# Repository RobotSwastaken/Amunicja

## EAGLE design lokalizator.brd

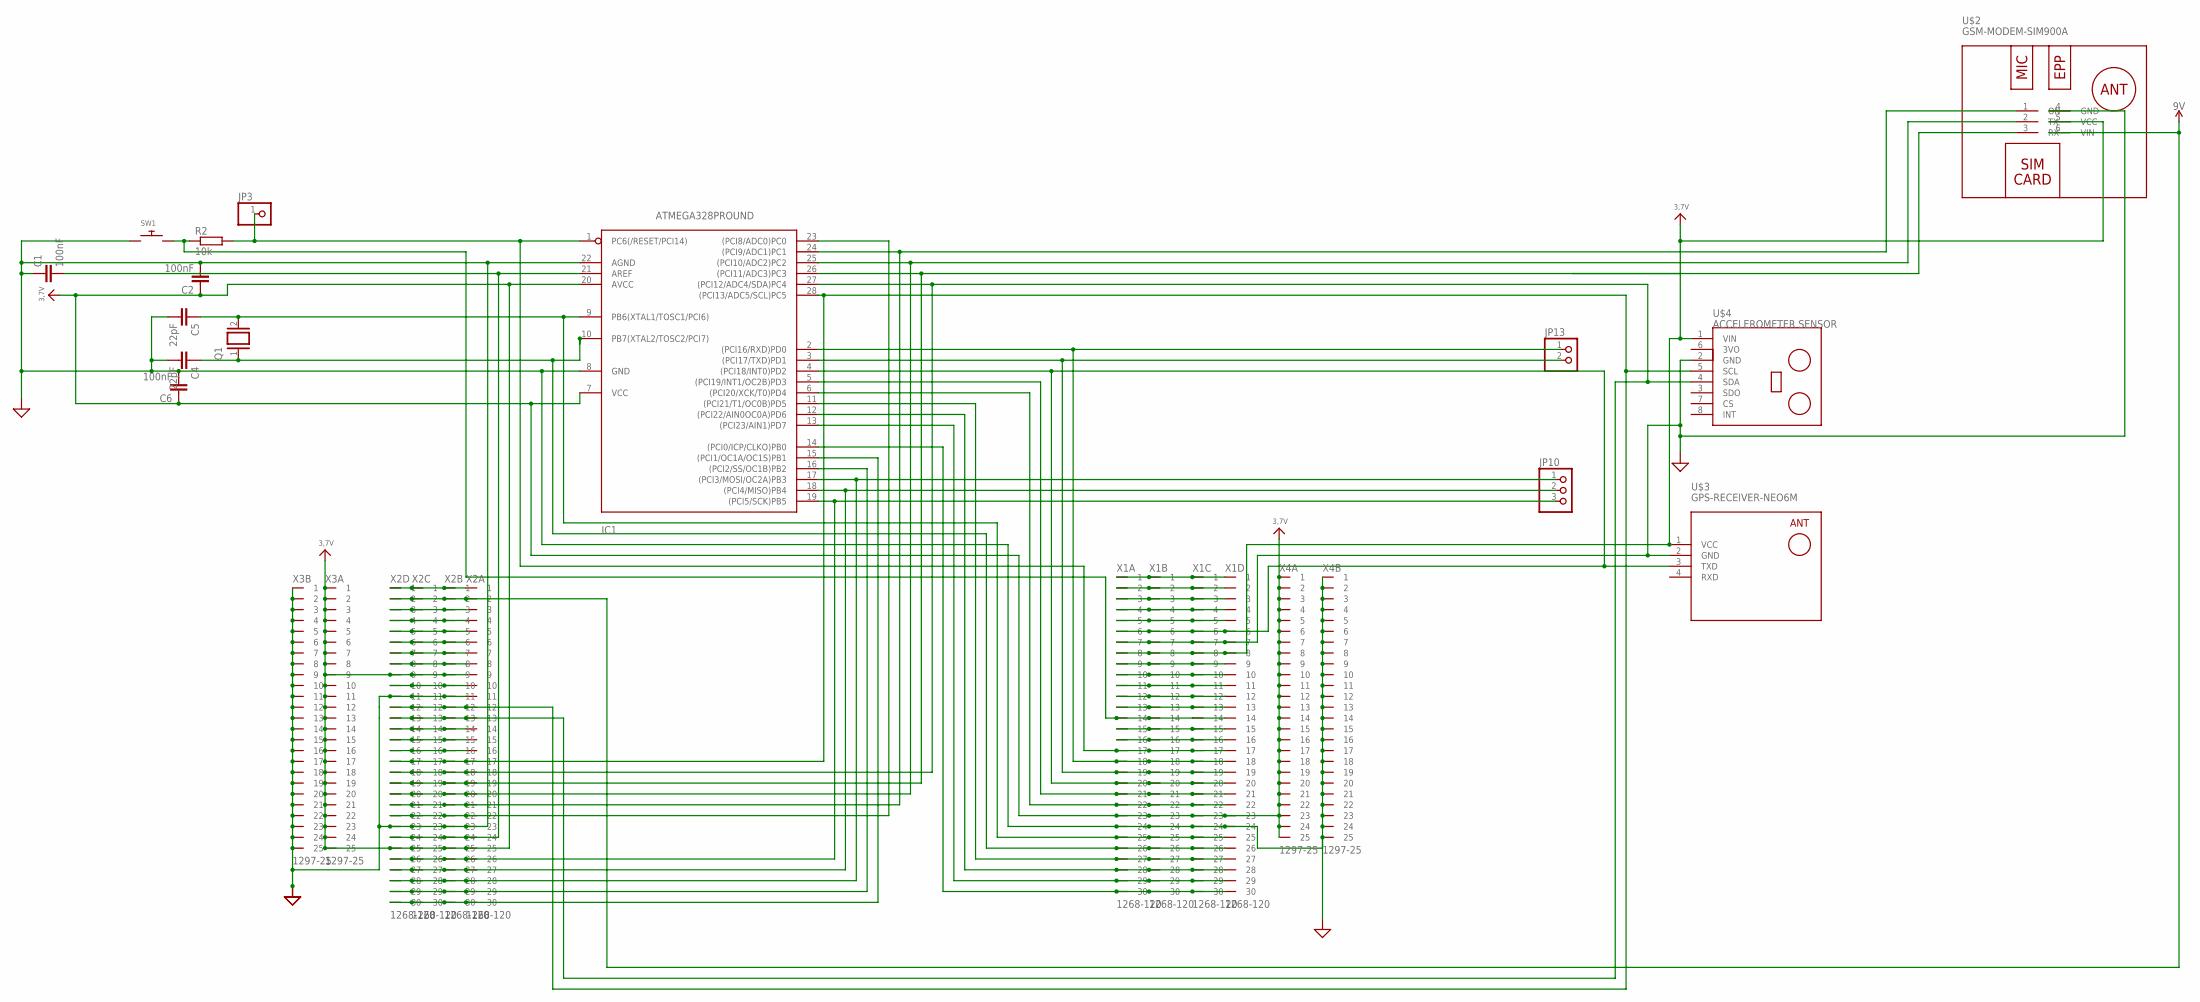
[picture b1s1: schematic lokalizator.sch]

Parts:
C1, C2, C6: 100nF; C2.5-3
C4, C5: 22pF; C2.5-3
IC1: ATMEGA328PROUND; DIL28-3-ROUND
JP3: PINHD-1X1; 1X01
JP10: PINHD-1X3; 1X03
JP13: PINHD-1X2; 1X02
Q1: XTAL; Q
R2: 10k; 0204/7
SW1: SWITCH_PUSHBUTTONEVQ-PE; TACT_PANA-EVQ
U$2: GSM-MODEM-SIM900A
U$3: GPS-RECEIVER-NEO6M
U$4: ACCELEROMETER SENSOR; LIGHT-SENSOR-BH1750
X1, X2: 1268-120
X3, X4: 1297-25

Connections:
3VO: U$4.6 (3VO)
GND: C1.1, C2.2, C4.2, C5.2, C6.2, IC1.8 (GND), IC1.22 (AGND), SW1.P$1, U$2.4 (GND), U$3.2 (GND), U$4.2 (GND), X1.A7 (7), X1.A24 (24), X1.B7 (7), X1.B24 (24), X1.C7 (7), X1.C24 (24), X1.D7 (7), X1.D24 (24), X2.A11 (11), X2.A23 (23), X2.B11 (11), X2.B23 (23), X2.C11 (11), X2.C23 (23), X2.D11 (11), X2.D23 (23), X3.B1 (1), X3.B2 (2), X3.B3 (3), X3.B4 (4), X3.B5 (5), X3.B6 (6), X3.B7 (7), X3.B8 (8), X3.B9 (9), X3.B10 (10), X3.B11 (11), X3.B12 (12), X3.B13 (13), X3.B14 (14), X3.B15 (15), X3.B16 (16), X3.B17 (17), X3.B18 (18), X3.B19 (19), X3.B20 (20), X3.B21 (21), X3.B22 (22), X3.B23 (23), X3.B24 (24), X3.B25 (25), X4.B1 (1), X4.B2 (2), X4.B3 (3), X4.B4 (4), X4.B5 (5), X4.B6 (6), X4.B7 (7), X4.B8 (8), X4.B9 (9), X4.B10 (10), X4.B11 (11), X4.B12 (12), X4.B13 (13), X4.B14 (14), X4.B15 (15), X4.B16 (16), X4.B17 (17), X4.B18 (18), X4.B19 (19), X4.B20 (20), X4.B21 (21), X4.B22 (22), X4.B23 (23), X4.B24 (24), X4.B25 (25)
unnamed: R2.1, SW1.P$2, X1.A14 (14), X1.B14 (14), X1.C14 (14), X1.D14 (14)
unnamed: IC1.1 (PC6(/RESET/PCI14)), JP3.1, R2.2, X1.A17 (17), X1.B17 (17), X1.C17 (17), X1.D17 (17)
unnamed: C1.2, IC1.21 (AREF), X2.A24 (24), X2.B24 (24), X2.C24 (24), X2.D24 (24)
unnamed: IC1.19 ((PCI5/SCK)PB5), JP10.3, X2.A26 (26), X2.B26 (26), X2.C26 (26), X2.D26 (26)
unnamed: C5.1, IC1.9 (PB6(XTAL1/TOSC1/PCI6)), Q1.2, X1.A25 (25), X1.B25 (25), X1.C25 (25), X1.D25 (25)
unnamed: C4.1, IC1.10 (PB7(XTAL2/TOSC2/PCI7)), Q1.1, X1.A26 (26), X1.B26 (26), X1.C26 (26), X1.D26 (26)
unnamed: IC1.18 ((PCI4/MISO)PB4), JP10.2, X2.A27 (27), X2.B27 (27), X2.C27 (27), X2.D27 (27)
unnamed: IC1.17 ((PCI3/MOSI/OC2A)PB3), JP10.1, X2.A28 (28), X2.B28 (28), X2.C28 (28), X2.D28 (28)
unnamed: IC1.14 ((PCI0/ICP/CLKO)PB0), X1.A30 (30), X1.B30 (30), X1.C30 (30), X1.D30 (30)
unnamed: IC1.28 ((PCI13/ADC5/SCL)PC5), U$4.5 (SCL), X2.A12 (12), X2.A17 (17), X2.B12 (12), X2.B17 (17), X2.C12 (12), X2.C17 (17), X2.D12 (12), X2.D17 (17)
unnamed: X1.A16 (16), X1.B16 (16), X1.C16 (16), X1.D16 (16)
unnamed: IC1.4 ((PCI18/INT0)PD2), U$3.3 (TXD), X1.A6 (6), X1.A20 (20), X1.B6 (6), X1.B20 (20), X1.C6 (6), X1.C20 (20), X1.D6 (6), X1.D20 (20)
unnamed: IC1.24 ((PCI9/ADC1)PC1), U$2.1 (ON), X2.A21 (21), X2.B21 (21), X2.C21 (21), X2.D21 (21)
unnamed: IC1.2 ((PCI16/RXD)PD0), JP13.1, X1.A18 (18), X1.B18 (18), X1.C18 (18), X1.D18 (18)
unnamed: IC1.3 ((PCI17/TXD)PD1), JP13.2, X1.A19 (19), X1.B19 (19), X1.C19 (19), X1.D19 (19)
unnamed: IC1.25 ((PCI10/ADC2)PC2), U$2.2 (TX), X2.A20 (20), X2.B20 (20), X2.C20 (20), X2.D20 (20)
unnamed: IC1.26 ((PCI11/ADC3)PC3), U$2.3 (RX), X2.A19 (19), X2.B19 (19), X2.C19 (19), X2.D19 (19)
unnamed: IC1.15 ((PCI1/OC1A/OC1S)PB1), X2.A30 (30), X2.B30 (30), X2.C30 (30), X2.D30 (30)
unnamed: IC1.16 ((PCI2/SS/OC1B)PB2), X2.A29 (29), X2.B29 (29), X2.C29 (29), X2.D29 (29)
unnamed: IC1.13 ((PCI23/AIN1)PD7), X1.A29 (29), X1.B29 (29), X1.C29 (29), X1.D29 (29)
unnamed: IC1.12 ((PCI22/AIN0OC0A)PD6), X1.A28 (28), X1.B28 (28), X1.C28 (28), X1.D28 (28)
unnamed: IC1.11 ((PCI21/T1/OC0B)PD5), X1.A27 (27), X1.B27 (27), X1.C27 (27), X1.D27 (27)
unnamed: IC1.23 ((PCI8/ADC0)PC0), X2.A22 (22), X2.B22 (22), X2.C22 (22), X2.D22 (22)
unnamed: IC1.5 ((PCI19/INT1/OC2B)PD3), X1.A21 (21), X1.B21 (21), X1.C21 (21), X1.D21 (21)
unnamed: IC1.27 ((PCI12/ADC4/SDA)PC4), U$4.4 (SDA), X2.A13 (13), X2.A18 (18), X2.B13 (13), X2.B18 (18), X2.C13 (13), X2.C18 (18), X2.D13 (13), X2.D18 (18)
unnamed: IC1.6 ((PCI20/XCK/T0)PD4), X1.A22 (22), X1.B22 (22), X1.C22 (22), X1.D22 (22)
unnamed: X1.A15 (15), X1.B15 (15), X1.C15 (15), X1.D15 (15)
unnamed: X1.A13 (13), X1.B13 (13), X1.C13 (13), X1.D13 (13)
unnamed: X1.A12 (12), X1.B12 (12), X1.C12 (12), X1.D12 (12)
unnamed: X1.A11 (11), X1.B11 (11), X1.C11 (11), X1.D11 (11)
unnamed: X1.A10 (10), X1.B10 (10), X1.C10 (10), X1.D10 (10)
unnamed: X1.A9 (9), X1.B9 (9), X1.C9 (9), X1.D9 (9)
unnamed: X1.A5 (5), X1.B5 (5), X1.C5 (5), X1.D5 (5)
unnamed: X1.A4 (4), X1.B4 (4), X1.C4 (4), X1.D4 (4)
unnamed: X1.A3 (3), X1.B3 (3), X1.C3 (3), X1.D3 (3)
unnamed: X1.A2 (2), X1.B2 (2), X1.C2 (2), X1.D2 (2)
unnamed: X1.A1 (1), X1.B1 (1), X1.C1 (1), X1.D1 (1)
unnamed: X2.A16 (16), X2.B16 (16), X2.C16 (16), X2.D16 (16)
unnamed: X2.A15 (15), X2.B15 (15), X2.C15 (15), X2.D15 (15)
unnamed: X2.A14 (14), X2.B14 (14), X2.C14 (14), X2.D14 (14)
unnamed: X2.A10 (10), X2.B10 (10), X2.C10 (10), X2.D10 (10)
unnamed: X2.A8 (8), X2.B8 (8), X2.C8 (8), X2.D8 (8)
unnamed: X2.A7 (7), X2.B7 (7), X2.C7 (7), X2.D7 (7)
unnamed: X2.A6 (6), X2.B6 (6), X2.C6 (6), X2.D6 (6)
unnamed: X2.A5 (5), X2.B5 (5), X2.C5 (5), X2.D5 (5)
unnamed: X2.A4 (4), X2.B4 (4), X2.C4 (4), X2.D4 (4)
unnamed: X2.A3 (3), X2.B3 (3), X2.C3 (3), X2.D3 (3)
unnamed: X2.A1 (1), X2.B1 (1), X2.C1 (1), X2.D1 (1)
RXD: U$3.4 (RXD)
VCC: C2.1, C6.1, IC1.7 (VCC), IC1.20 (AVCC), U$2.5 (VCC), U$2.6 (VIN), U$3.1 (VCC), U$4.1 (VIN), X1.A8 (8), X1.A23 (23), X1.B8 (8), X1.B23 (23), X1.C8 (8), X1.C23 (23), X1.D8 (8), X1.D23 (23), X2.A2 (2), X2.A9 (9), X2.A25 (25), X2.B2 (2), X2.B9 (9), X2.B25 (25), X2.C2 (2), X2.C9 (9), X2.C25 (25), X2.D2 (2), X2.D9 (9), X2.D25 (25), X3.A1 (1), X3.A2 (2), X3.A3 (3), X3.A4 (4), X3.A5 (5), X3.A6 (6), X3.A7 (7), X3.A8 (8), X3.A9 (9), X3.A10 (10), X3.A11 (11), X3.A12 (12), X3.A13 (13), X3.A14 (14), X3.A15 (15), X3.A16 (16), X3.A17 (17), X3.A18 (18), X3.A19 (19), X3.A20 (20), X3.A21 (21), X3.A22 (22), X3.A23 (23), X3.A24 (24), X3.A25 (25), X4.A1 (1), X4.A2 (2), X4.A3 (3), X4.A4 (4), X4.A5 (5), X4.A6 (6), X4.A7 (7), X4.A8 (8), X4.A9 (9), X4.A10 (10), X4.A11 (11), X4.A12 (12), X4.A13 (13), X4.A14 (14), X4.A15 (15), X4.A16 (16), X4.A17 (17), X4.A18 (18), X4.A19 (19), X4.A20 (20), X4.A21 (21), X4.A22 (22), X4.A23 (23), X4.A24 (24), X4.A25 (25)

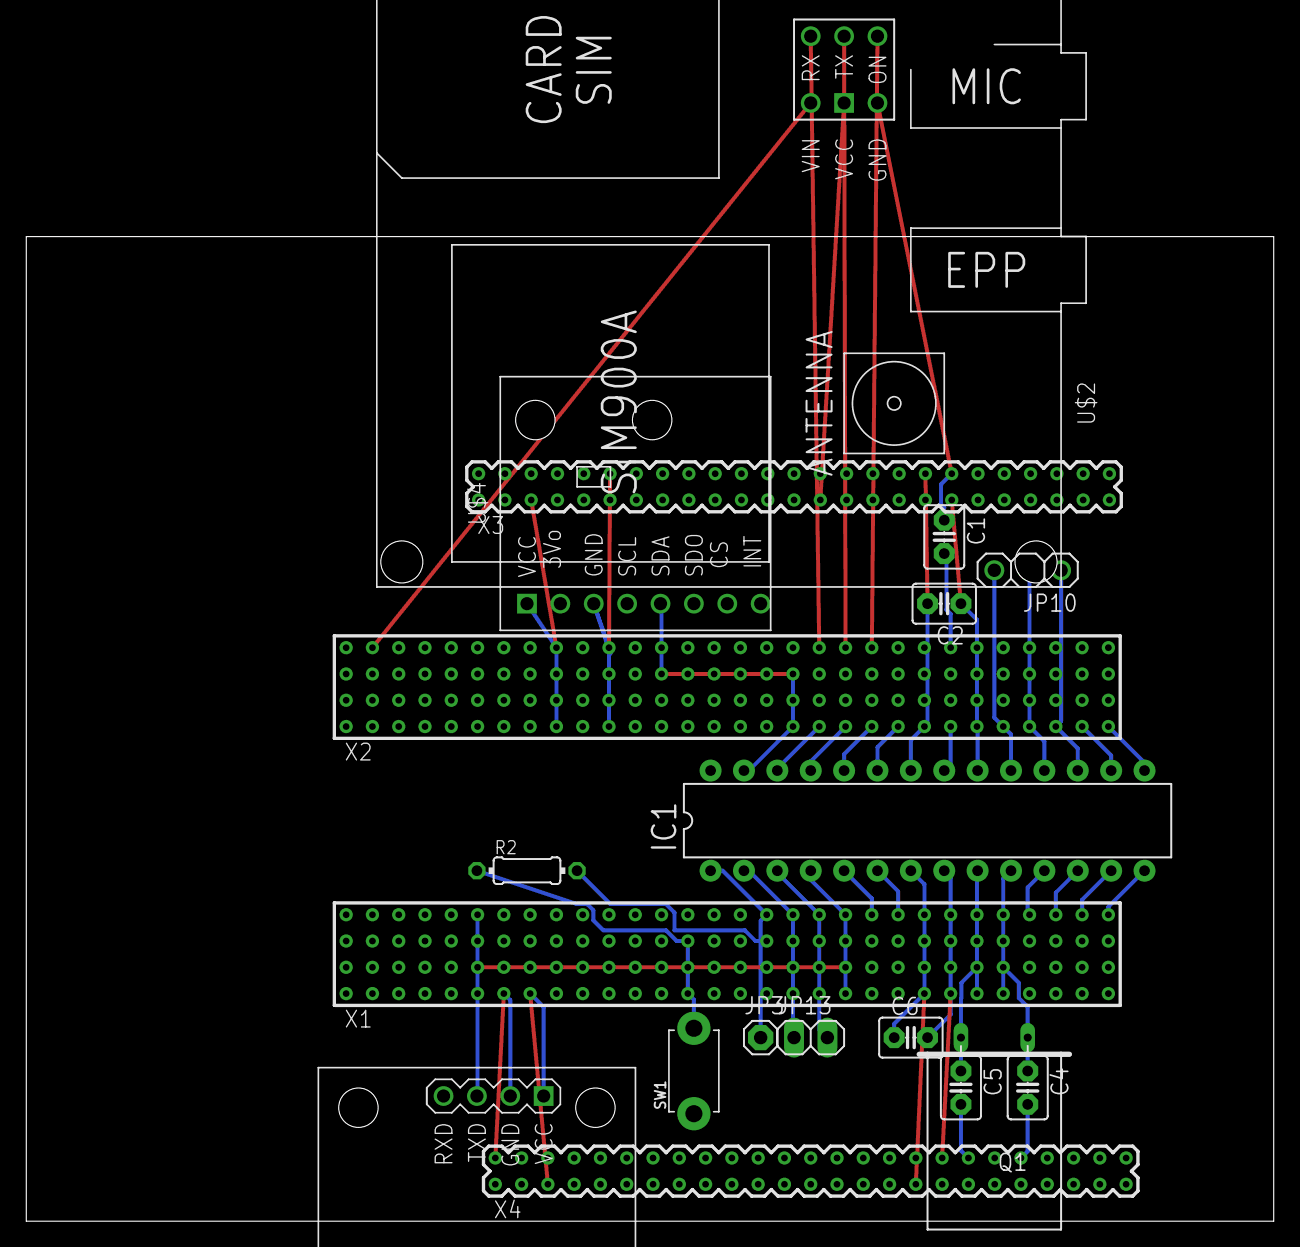
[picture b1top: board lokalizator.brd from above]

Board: 2 copper layers, 94.9 x 74.9 mm, 19 parts (0 on the bottom side), 50 nets.

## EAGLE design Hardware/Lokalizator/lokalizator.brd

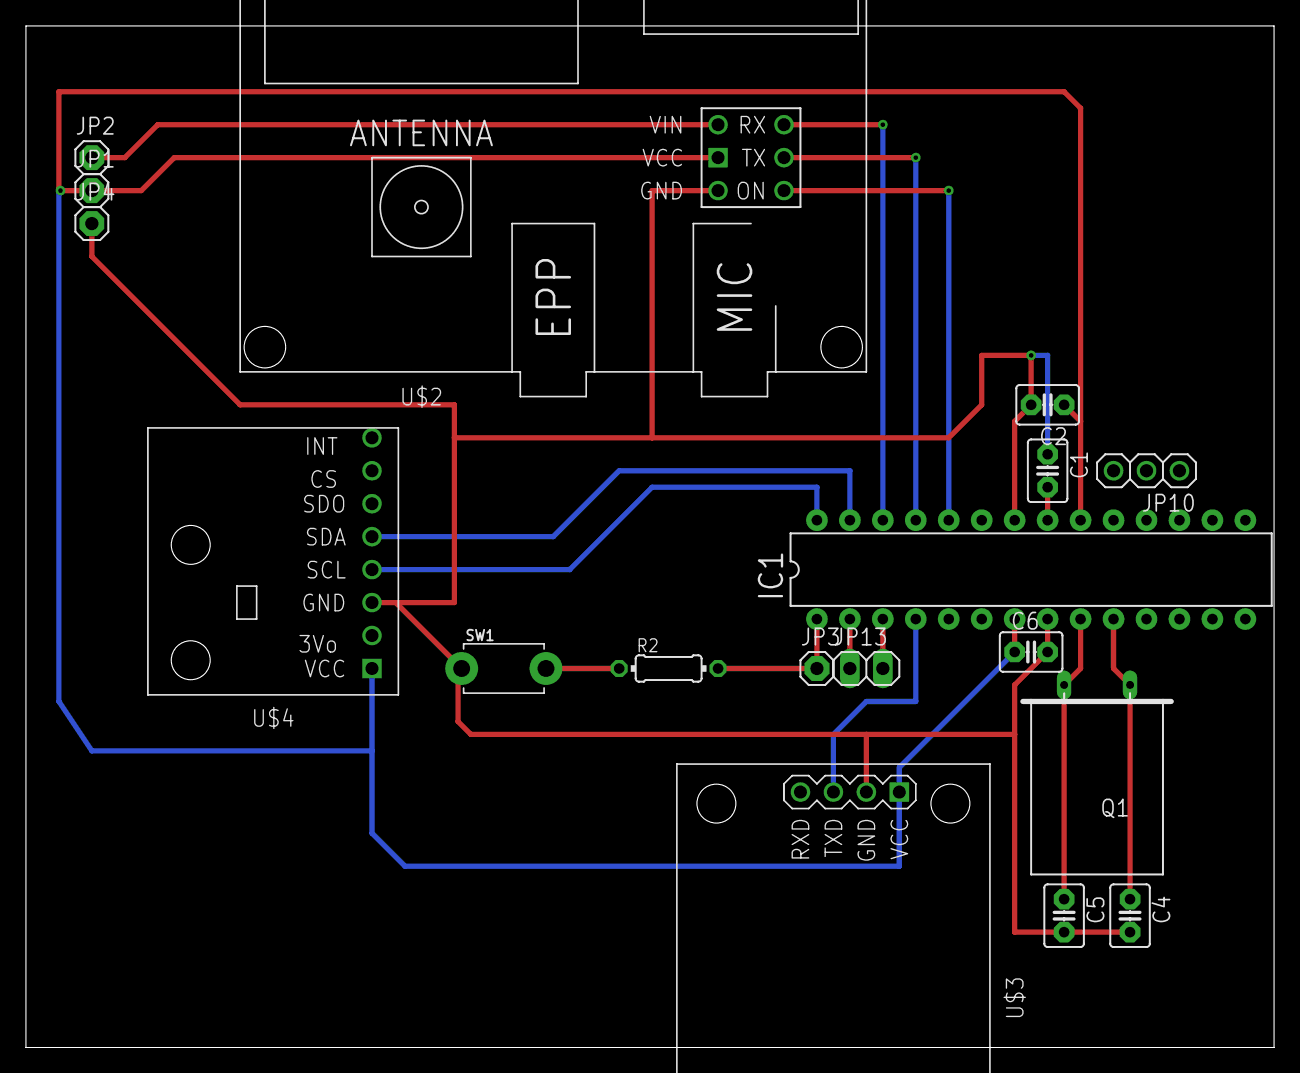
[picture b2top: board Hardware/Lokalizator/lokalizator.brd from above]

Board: 2 copper layers, 96.2 x 78.7 mm, 18 parts (0 on the bottom side), 18 nets.

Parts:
C1, C2, C6: 100nF; C2.5-3
C4, C5: 22pF; C2.5-3
IC1: ATMEGA328PROUND; DIL28-3-ROUND
JP1, JP2, JP3, JP4: 1X01
JP10: 1X03
JP13: 1X02
Q1: Q
R2: 10k; 0204/7
SW1: TACT_PANA-EVQ
U$2: GSM-MODULE-G510; GSM-MODEM-SIM900A
U$3: GPS-RECEIVER-NEO6M
U$4: ACCELEROMETER SENSOR; LIGHT-SENSOR-BH1750

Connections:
GND: C1.1, C2.2, C4.2, C5.2, C6.2, IC1.8, IC1.22, JP4.1, SW1.P$1, U$2.4, U$3.2, U$4.2
unnamed: IC1.1, JP3.1, R2.2
unnamed: C1.2, IC1.21
unnamed: IC1.19, JP10.3
unnamed: C5.1, IC1.9, Q1.2
unnamed: IC1.18, JP10.2
unnamed: IC1.17, JP10.1
unnamed: C4.1, IC1.10, Q1.1
unnamed: IC1.27, U$4.4
unnamed: IC1.4, U$3.3
unnamed: IC1.24, U$2.1
unnamed: IC1.2, JP13.1
unnamed: IC1.3, JP13.2
unnamed: IC1.25, U$2.2
unnamed: IC1.26, U$2.3
unnamed: IC1.28, U$4.5
unnamed: R2.1, SW1.P$2
VCC: C2.1, C6.1, IC1.7, IC1.20, JP1.1, JP2.1, U$2.5, U$2.6, U$3.1, U$4.1

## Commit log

2017-02-06 :boom::camel: Added .gitattributes

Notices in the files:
parts and their libraries:
diy-modules2: Released under the Creative Commons Attribution 4.0 International License: http://creativecommons.org/licenses/by/4.0
SparkFun-PowerSymbols: Licensing: Creative Commons ShareAlike 4.0 International - https://creativecommons.org/licenses/by-sa/4.0
